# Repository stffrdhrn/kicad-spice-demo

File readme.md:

## Demo of Kicad Circuit Simulation in Ngspice & NgNutmeg

Source project for the kicad circuit used in my blog post on [simulating kicad schematics in spice](http://stffrdhrn.github.io/electronics/2015/04/28/simulating_kicad_schematics_in_spice.html). 

The circuit is a simple dual supply non inverting op amp. 

### Pictures

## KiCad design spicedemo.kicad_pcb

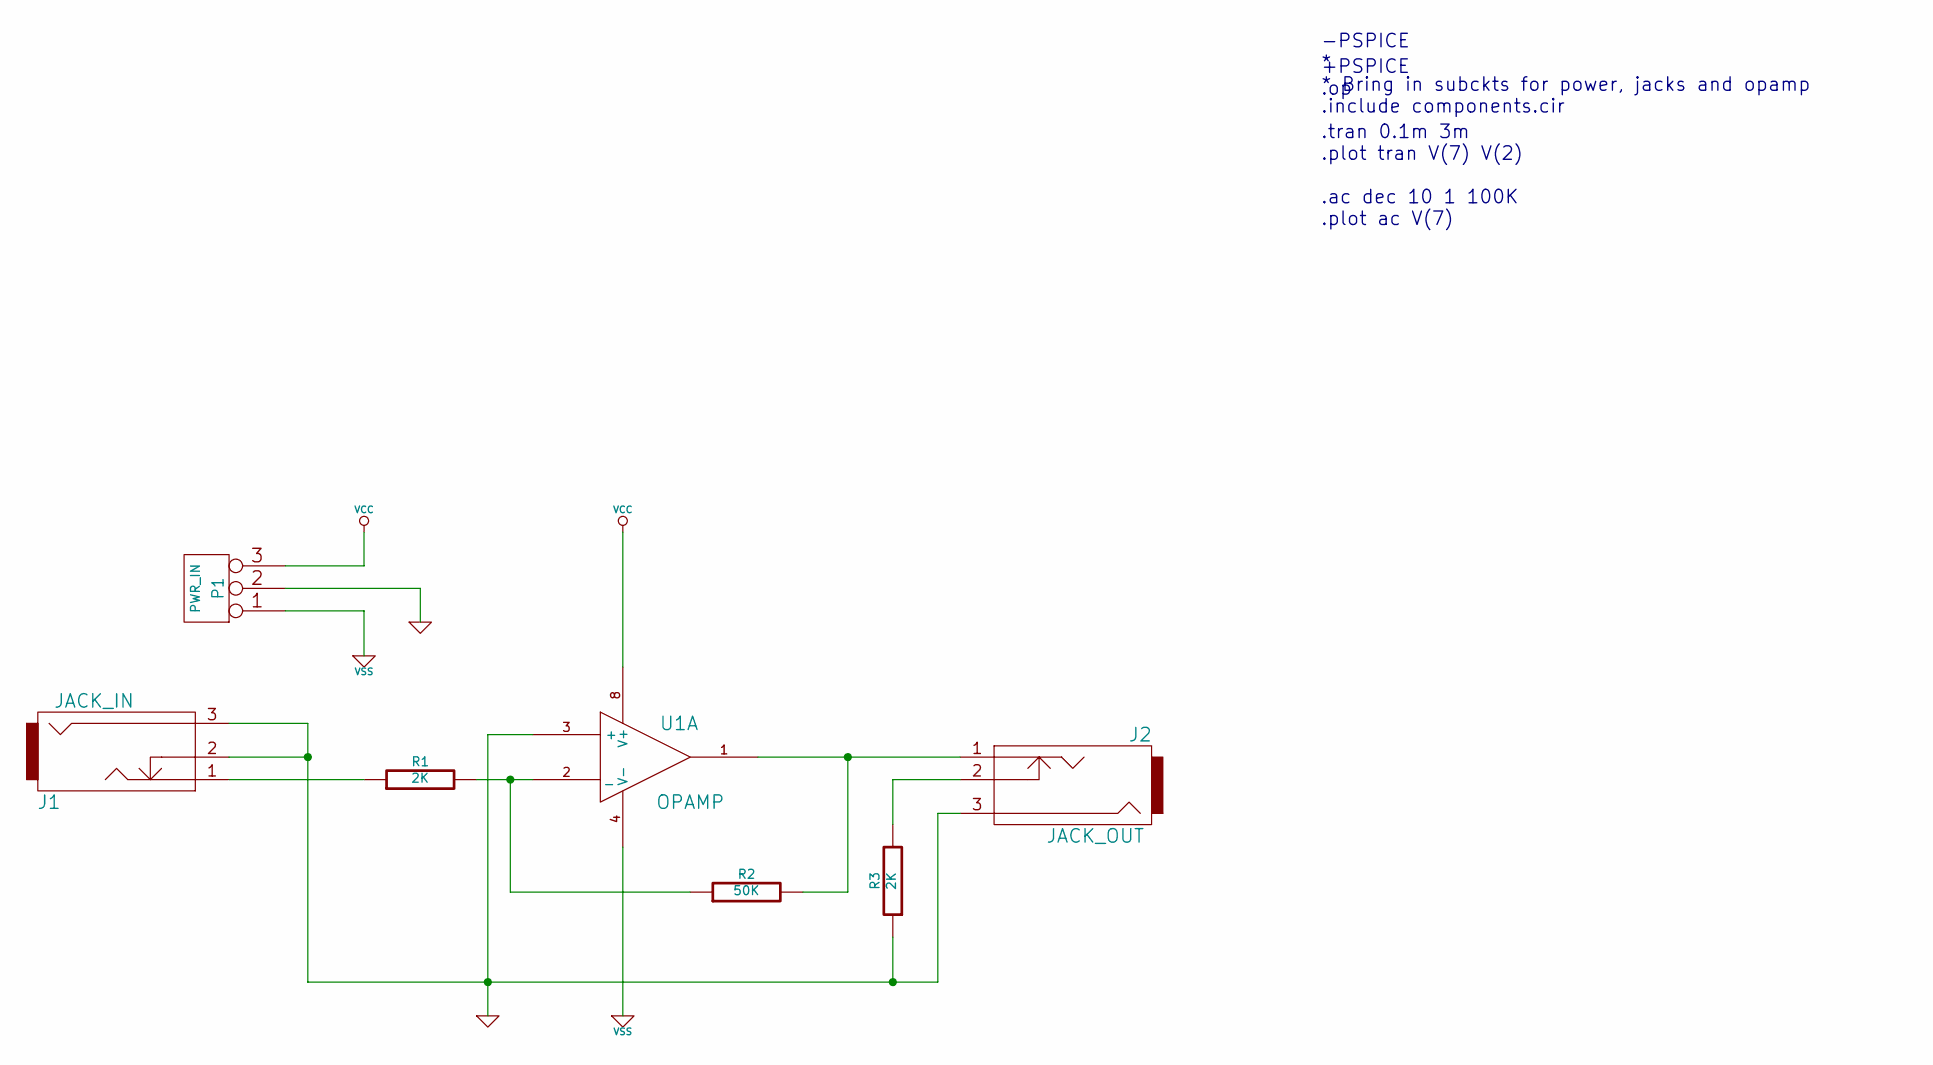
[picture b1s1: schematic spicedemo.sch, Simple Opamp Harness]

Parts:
J1: JACK_IN
J2: JACK_OUT
P1: PWR_IN
R1, R3: 2K
R2: 50K
U1: OPAMP

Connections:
GND: J1.2, J1.3, J2.3, P1.2 (PM), R3.1, U1.3 (+)
unnamed: J1.1, R1.1
unnamed: J2.2, R3.2
unnamed: R1.2, R2.1, U1.2 (_)
unnamed: J2.1, R2.2, U1.1
VCC: P1.3, U1.8 (V+)
VSS: P1.1, U1.4 (V-)

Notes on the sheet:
+PSPICE .op .tran 0.1m 3m .plot tran V(7) V(2) .ac dec 10 1 100K .plot ac V(7)
-PSPICE * * Bring in subckts for power, jacks and opamp .include components.cir

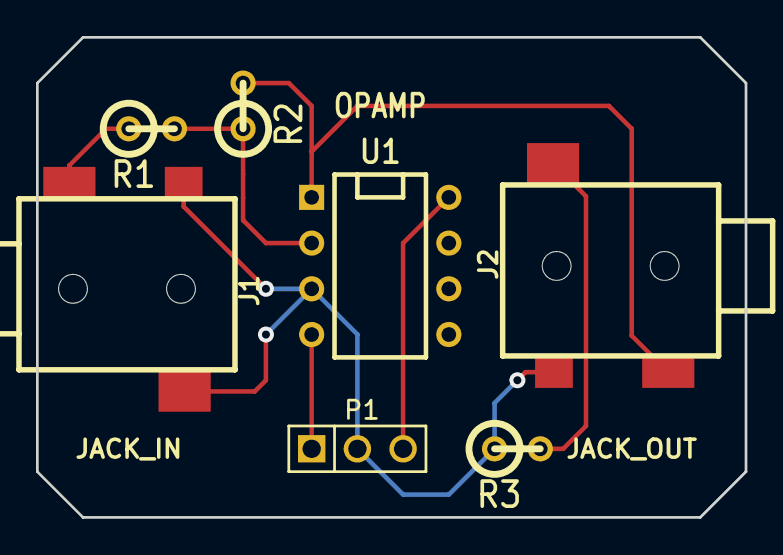
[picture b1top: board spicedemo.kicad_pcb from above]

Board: 2 copper layers, 39.4 x 26.7 mm, 7 parts (0 on the bottom side), 7 nets.

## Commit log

2015-04-30 dont need that cir filewq
2015-04-30 add readme
2015-04-30 add schematic image
